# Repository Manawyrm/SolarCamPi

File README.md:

# SolarCamPi

__Detailed information at https://tbspace.de/solarcampi.html__

BOM (PCB-RevC):  
https://tbspace.de/content/downloads/ibom_solarcampi_revc.html

Firmware (PCB-RevB/RevC):  
https://github.com/Manawyrm/SolarCamPi/tree/master/firmware

Schematic (PCB-RevC):  
https://github.com/Manawyrm/SolarCamPi/blob/master/pcb/solarcampi.pdf

Raspberry Pi can flash the AVR, using [avrdude with LinuxSPI support](https://github.com/kcuzner/avrdude) and _inverted_ GPIO 17 as reset.

avrdude.conf configuration entry: 
```
programmer 
  id       = "linuxspi";
  desc     = "Use Linux SPI device in /dev/spidev*";
  type     = "linuxspi";
  reset    = ~ 17;
  baudrate = 40000;
;
```

avrdude Usage to flash firmware:  
`avrdude -p m328p -P /dev/spidev0.0 -c linuxspi -U flash:w:firmware.hex`
  
avrdude Usage to set fuses:  
`avrdude -p m328p -P /dev/spidev0.0 -c linuxspi -U lfuse:w:0xe2:m -U hfuse:w:0xd9:m -U efuse:w:0xfd:m`

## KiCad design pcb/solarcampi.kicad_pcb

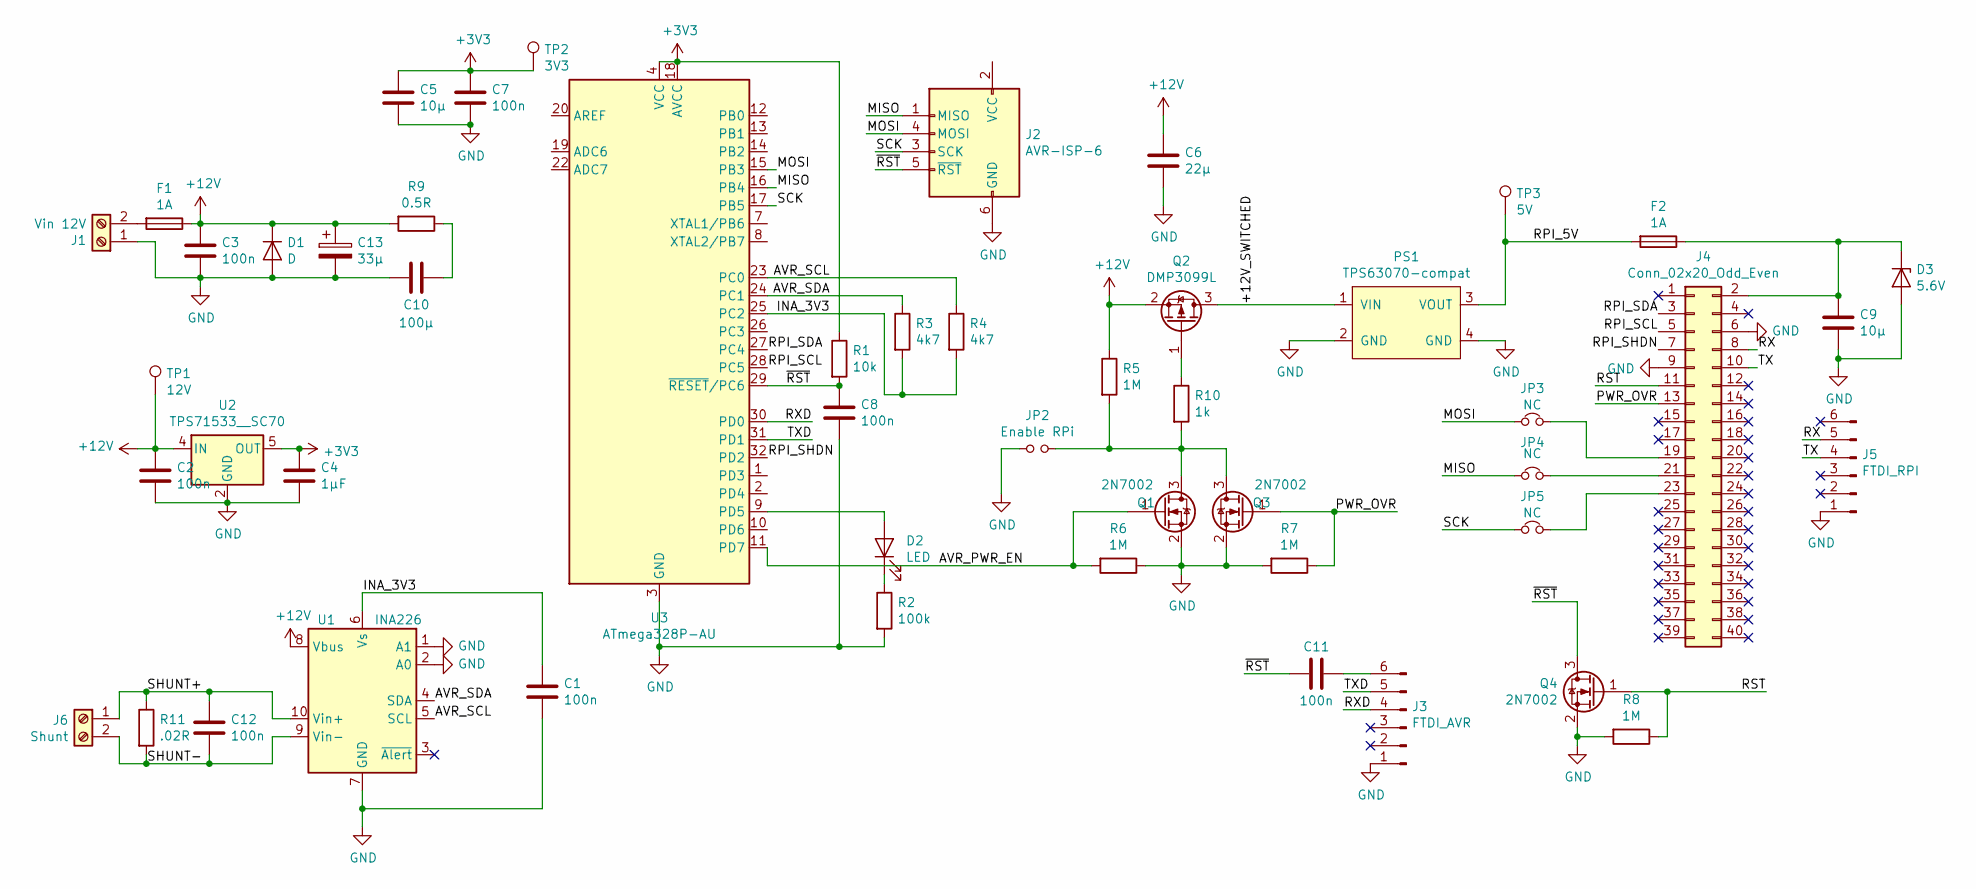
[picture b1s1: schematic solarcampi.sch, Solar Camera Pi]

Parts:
C1, C2, C3, C7, C8, C11, C12: 100n; C_0805_2012Metric_Pad1.15x1.40mm_HandSolder
C4: 1µF; C_0805_2012Metric_Pad1.15x1.40mm_HandSolder
C5, C9: 10µ; C_0805_2012Metric_Pad1.15x1.40mm_HandSolder
C6: 22µ; C_0805_2012Metric_Pad1.15x1.40mm_HandSolder
C10: 100µ; C_1210_3225Metric_Pad1.42x2.65mm_HandSolder
C13: 33µ; CP_Elec_5x5.4
D1: D; D_SOD-123
D2: LED; LED_0805_2012Metric_Pad1.15x1.40mm_HandSolder
D3: 5.6V; D_SOD-123
F1: 1A; Fuse_SMD_HASF
F2: 1A; Fuse_0805_2012Metric_Pad1.15x1.40mm_HandSolder
J1: Vin 12V; TerminalBlock_bornier-2_P5.08mm
J2: AVR-ISP-6; IDC-Header_2x03_P2.54mm_Vertical
J3: FTDI_AVR; PinHeader_1x06_P2.54mm_Vertical
J4: Conn_02x20_Odd_Even; PinHeader_2x20_P2.54mm_Vertical
J5: FTDI_RPI; PinHeader_1x06_P2.54mm_Vertical
J6: Shunt; TerminalBlock_bornier-2_P5.08mm
JP2: Enable RPi; PinHeader_1x02_P2.54mm_Vertical
JP3, JP4, JP5: NC; SolderJumper-2_P1.3mm_Bridged_Pad1.0x1.5mm
PS1: TPS63070-compat; TPS63070-module-compat
Q1, Q3, Q4: 2N7002; SOT-23
Q2: DMP3099L; SOT-23
R1: 10k; R_0805_2012Metric_Pad1.15x1.40mm_HandSolder
R2: 100k; R_0805_2012Metric_Pad1.15x1.40mm_HandSolder
R3, R4: 4k7; R_0805_2012Metric_Pad1.15x1.40mm_HandSolder
R5, R6, R7, R8: 1M; R_0805_2012Metric_Pad1.15x1.40mm_HandSolder
R9: 0.5R; R_1210_3225Metric_Pad1.42x2.65mm_HandSolder
R10: 1k; R_0805_2012Metric_Pad1.15x1.40mm_HandSolder
R11: .02R; R_1210_3225Metric_Pad1.42x2.65mm_HandSolder
TP1: 12V; TestPoint_Pad_1.0x1.0mm
TP2: 3V3; TestPoint_Pad_1.0x1.0mm
TP3: 5V; TestPoint_Pad_1.0x1.0mm
U1: INA226; MSOP-10_3x3mm_P0.5mm
U2: TPS71533__SC70; SOT-353_SC-70-5_Handsoldering
U3: ATmega328P-AU; TQFP-32_7x7mm_P0.8mm

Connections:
+3V3: C4.1, C5.1, C7.1, R1.1, TP2.1, U2.5 (OUT), U3.4 (VCC), U3.6 (VCC), U3.18 (AVCC)
+12V: C2.1, C3.1, C6.2, C13.1, D1.1 (K), F1.1, Q2.2 (S), R5.1, R9.2, TP1.1, U1.8 (Vbus), U2.4 (IN)
/+12V_SWITCHED: PS1.1 (VIN), Q2.3 (D)
/AVR_PWR_EN: Q1.1 (G), R6.2, U3.11 (PD7)
/AVR_SCL: R4.1, U1.5 (SCL), U3.23 (PC0)
/AVR_SDA: R3.1, U1.4 (SDA), U3.24 (PC1)
/INA_3V3: C1.1, R3.2, R4.2, U1.6 (Vs), U3.25 (PC2)
/MISO: J2.1 (MISO), JP4.1, U3.16 (PB4)
/MOSI: J2.4 (MOSI), JP3.1, U3.15 (PB3)
/PWR_OVR: J4.13, Q3.1 (G), R7.1
/RPI_5V: F2.2, PS1.3 (VOUT), TP3.1
/RPI_SCL: J4.5, U3.28 (PC5)
/RPI_SDA: J4.3, U3.27 (PC4)
/RPI_SHDN: J4.7, U3.32 (PD2)
/RST: J4.11, Q4.1 (G), R8.1
/RX: J4.8, J5.5
/RXD: J3.4, U3.30 (PD0)
/SCK: J2.3 (SCK), JP5.1, U3.17 (PB5)
/SHUNT+: C12.1, J6.1, R11.1, U1.10 (Vin+)
/SHUNT-: C12.2, J6.2, R11.2, U1.9 (Vin-)
/TX: J4.10, J5.4
/TXD: J3.5, U3.31 (PD1)
/~RST: C8.1, C11.2, J2.5 (~RST), Q4.3 (D), R1.2, U3.29 (~RESET~/PC6)
GND: C1.2, C2.2, C3.2, C4.2, C5.2, C6.1, C7.2, C8.2, C9.2, C10.1, C13.2, D1.2 (A), D3.2 (A), J1.1, J2.6 (GND), J3.1, J4.6, J4.9, J5.1, JP2.1, PS1.2 (GND), PS1.4 (GND), Q1.2 (S), Q3.2 (S), Q4.2 (S), R2.2, R6.1, R7.2, R8.2, U1.1 (A1), U1.2 (A0), U1.7 (GND), U2.2 (GND), U3.3 (GND), U3.5 (GND), U3.21 (GND)
unnamed: C9.1, D3.1 (K), F2.1, J4.2
unnamed: C10.2, R9.1
unnamed: C11.1, J3.6
unnamed: D2.1 (K), R2.1
unnamed: D2.2 (A), U3.9 (PD5)
unnamed: F1.2, J1.2
unnamed: J4.19, JP3.2
unnamed: J4.21, JP4.2
unnamed: J4.23, JP5.2
unnamed: JP2.2, Q1.3 (D), Q3.3 (D), R5.2, R10.2
unnamed: Q2.1 (G), R10.1

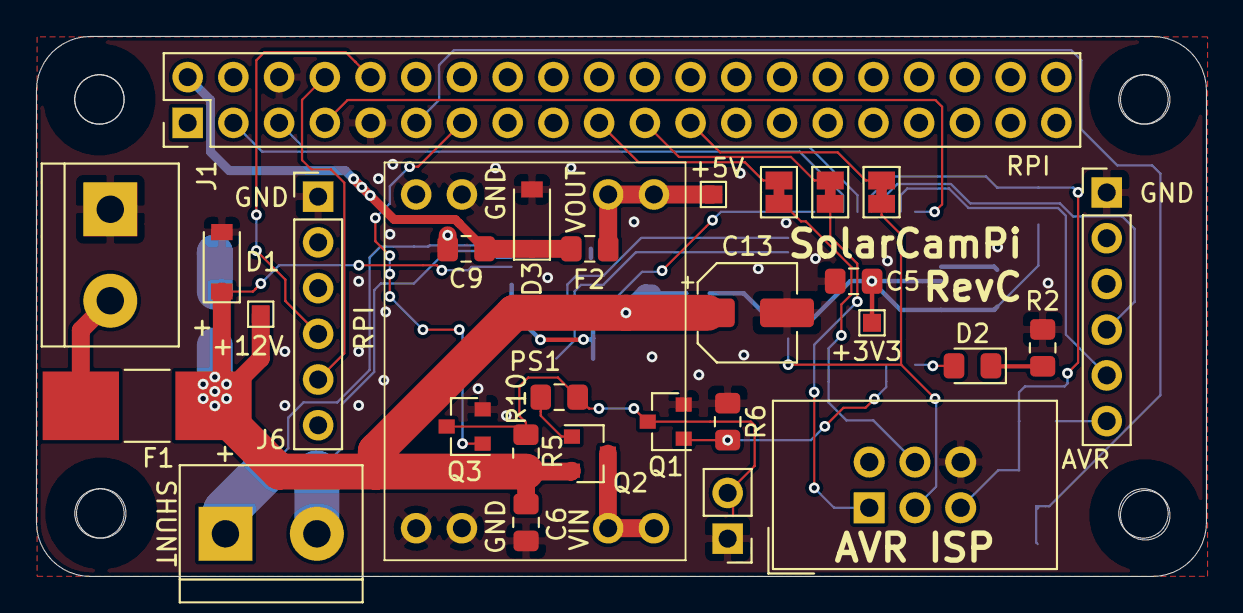
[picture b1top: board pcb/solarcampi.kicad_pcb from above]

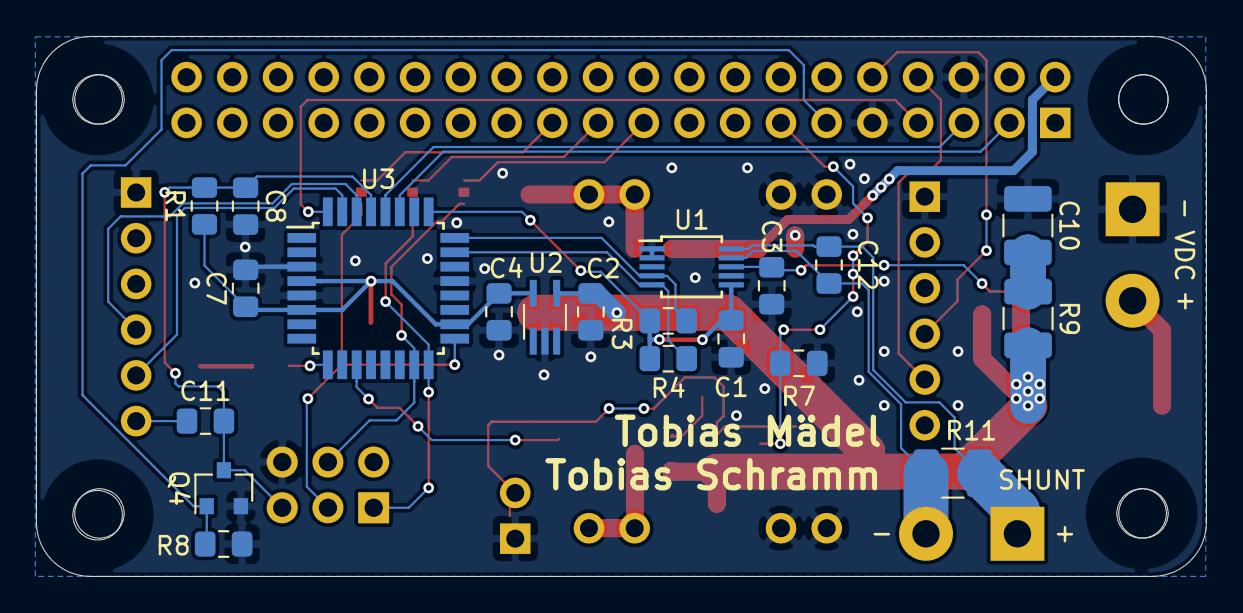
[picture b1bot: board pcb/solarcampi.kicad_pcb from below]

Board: 2 copper layers, 65.0 x 30.0 mm, 50 parts (20 on the bottom side), 35 nets.

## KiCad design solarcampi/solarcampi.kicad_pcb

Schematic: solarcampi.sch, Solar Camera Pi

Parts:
C1, C2, C3, C5, C6: 100n; C_0805_2012Metric_Pad1.15x1.40mm_HandSolder
C4: 1µF; C_0805_2012Metric_Pad1.15x1.40mm_HandSolder
C7, C8: 10µ; C_0805_2012Metric_Pad1.15x1.40mm_HandSolder
F1: 1A; Fuse_SMD_HASF
J1: Conn_02x20_Odd_Even; PinHeader_2x20_P2.54mm_Vertical
J2: Vin 12V; TerminalBlock_bornier-2_P5.08mm
J3: AVR-ISP-6; IDC-Header_2x03_P2.54mm_Vertical
J4: FTDI; PinHeader_1x06_P2.54mm_Vertical
JP1: Jumper_2_Open; SolderJumper-2_P1.3mm_Open_Pad1.0x1.5mm
PS1: MP1584EN; MP1584_buck_module
Q1: IRLML 2244; SOT-23
Q2: BCR 108 SMD; SOT-23
R1, R2: 10k; R_0805_2012Metric_Pad1.15x1.40mm_HandSolder
R3, R4: 4k7; R_0805_2012Metric_Pad1.15x1.40mm_HandSolder
U1: INA226; MSOP-10_3x3mm_P0.5mm
U2: ATmega328P-AU; TQFP-32_7x7mm_P0.8mm
U3: TPS71533__SC70; SOT-353_SC-70-5_Handsoldering

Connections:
+3V3: C2.1, C4.1, C7.1, JP1.1, R2.1, U2.4, U2.6, U2.18, U3.5 (OUT)
+12V: C1.1, C3.1, F1.1, Q1.2 (S), R1.1, U1.8 (Vbus), U3.4 (IN)
+12VA: PS1.1 (VIN), Q1.3 (D)
/AVR_I2C_PULLUP: R3.2, R4.2, U2.19
/AVR_SCL: R4.1, U1.5 (SCL), U2.23
/AVR_SDA: R3.1, U1.4 (SDA), U2.24
/INA_3V3: C5.1, U1.6 (Vs), U2.10
/MISO: J3.1, U2.16
/MOSI: J3.4, U2.15
/RPI_SCL: J1.5, U2.28
/RPI_SDA: J1.3, U2.27
/RPI_SHDN: J1.7, U2.32
/RX: J1.8, J4.5
/SCK: J3.3, U2.17
/TX: J1.10, J4.4
/~RST: C6.1, J3.5, R2.2, U2.29
GND: C1.2, C2.2, C3.2, C4.2, C5.2, C6.2, C7.2, C8.2, J1.6, J2.1, J3.6, J4.1, PS1.2 (VINGND), PS1.3 (VOUTGND), Q2.2 (E), U1.1 (A1), U1.2 (A0), U1.7 (GND), U2.3, U2.5, U2.21, U3.2 (GND)
unnamed: C8.1, J1.2, PS1.4 (VOUT)
unnamed: F1.2, J2.2
unnamed: J3.2, JP1.2
unnamed: Q1.1 (G), Q2.3 (C), R1.2
unnamed: Q2.1 (B), U2.11

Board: 2 copper layers, 24 parts (10 on the bottom side), 22 nets, no tracks yet.

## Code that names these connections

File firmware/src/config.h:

#pragma once

#define AVR_SCL 14 // INA220 Software I2C
#define AVR_SDA 15 // INA220 Software I2C
//#define AVR_I2C_PULLUP 20 // INA220 Software I2C
#define INA_3V3 16 // INA220 Power

#define AVR_PWR_EN 7 // MOSFET to enable RPi supply rail
#define RPI_SHDN 2   // Shutdown signalling from RPi
#define LED 5

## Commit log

2019-05-27 Create LICENSE
2019-05-29 Add fuse, add decoupling caps, set footprints
2019-05-30 Add ISP header, FTDI header, more caps, power switching for INA and 2 I2C busses
2019-05-31 Component placement v1
2019-05-31 Route everything
2019-05-31 RevA finished
2019-06-06 add firmware
2019-06-06 rename firmware
2019-06-08 works \o/
2019-06-08 add timeout, voltage readback
2019-06-09 Fixed I2C Write
2019-06-09 add EEPROM support
2019-06-09 fix I2C after sleep, update todo
2019-06-16 Schematic RevB
2019-06-16 Layout RevB
2019-06-16 Add PCB-art
2019-06-16 Add 2-pin screw terminal with 3d model
2019-06-16 Minor aesthetic fixups
2019-06-16 Add more GND pins to reduce GND loop area
2019-06-19 Widen throughholes for regulator footprint to 1 mm
2019-06-19 Add pin headers to power module
2019-07-24 Add interactive BOM
2019-07-24 rename
2019-07-24 Add readme
2019-07-25 Firmware updated for RevB pcb
2019-07-25 Add new photo of RevB
2019-07-25 Updated readSetting tool
2019-07-26 Add charge current measurement
2019-07-26 Fix RevB errata
    - Fix SOT23 NMOS pinout
    - Fix AVR reset circuitry
    - Add ceramic snubber to suppress ringing at input
2019-07-26 Optimize GND around C11
2019-07-27 Add current shunt
2019-07-27 Update 3d models
2019-07-27 Update revision indictor to `RevC`
2019-07-27 Add big electrolytic cap for further suppression of ringing
2019-07-27 Optimize GND connectivity
2019-07-27 Finishing touches on RevC
2019-07-27 Update readme to RevC
2022-04-03 Update firmware
2022-04-03 Add CI workflow
2022-04-04 Remove disabled folder
2022-04-04 CI: publish release binaries
2022-04-06 Add timestamp keeping
